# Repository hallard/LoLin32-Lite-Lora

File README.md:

# ESP32 LoLin32 Lite Lora Shield for RFM95 or RN2483

This shield is used to hold LoRa modules such as HopeRF [RFM95][4] or Mictrochip [RN2483][7] with WeMos ESP32 [LoLin32-Lite][22] boards it has the followong features:
- I2C Pullups placement
- Classic I2C connector with SCL/SDA and 3V3/GND reversable pin by solder pad
- Groove I2C connector
- Footprint for RFM95/96/98 or RN2483/RN2903 Lora module
- Footprint for choosing single Wire, SMA or u-FL Antenna type 
- 1 x WS2812B Type LED for visual indication
- 1 x Push Button
- Added footprint for Microchip 24AA02E64 64 bits serial number (DEVEUI)

Take care that WeMos has different Lolin32 boards, you need the [Lite][22] model. They Provide WeMos [Lolin32][20], [Lolin32 Pro][21] or this one [Lolin32 Lite][22]

You can also check the shield for the [Lolin32 (not Lite)][9] classic version. 

# Detailed Description

Look at the schematics for more informations.

SPI connexion is classic (MOSI/MISO/CLK), 

Other pins that may need be adapted into code (for example if you use TTN network gateway code) according to the following pinout

```
Lolin32-Lite   RFM9x Module
  IO5   <-------> SEL 
  IO19  <-------> MISO
  IO23  <-------> MOSI
  IO18  <-------> CLK
  IO27  <-------> DIO0
  IO26  <-------> DIO1
  IO4   <-------> DIO2
  IO25  <-------> RST
  IO35  <-------> DIO5

Lolin32-Lite   RN2xx3 Module
  IO4   <-------> RESET
  IO25  <-------> RX
  IO35  <-------> TX

Lolin32-Lite   Shield Feature
  IO12  <-------> I2C SCL
  IO14  <-------> I2C SDA
  IO13  <-------> WS2812 LEDS
  IO15  <-------> Push Button

Lolin32-Lite Free I/O
  IO0  -> Also used for Flash
  IO2 
  IO16 
  IO17
  IO22 -> On Board LoLin32-Lite LED
  IO32
  IO33 
  IO34 
```

**Do not forget to join (solder) the correct LoRa antenna trace** depending on module you place (RFM95 or RN2483), see picture below.

And as classic advice, **connect the LoRa antenna before powering** the board to avoid any damage to LoRa module

# Schematic  

# Firmware  

There is no firmware available, but you can have a large demo of features and a full working LoRa node (with RFM95) with this excellent [ESP32-Paxcounter](https://github.com/cyberman54/ESP32-Paxcounter/) software, it's a must see.

# Boards  

&nbsp;

You can order the PCB of this board at [PCBs.io][8]. PCBs.io give me some reward when you order my designed boards from their site. This is pretty good, because I can use these rewards to create and design new boards and order them for free, so if you don't care about PCB manufacturer please use PCBs.io.

# Assembled boards (TBD)

Not assembled yet but you can see approx what it looks like with the [Lolin32 (not Lite)][9] version. 

## With RFM95

## With RN2483

# License

This work is licensed under a [Creative Commons Attribution-NonCommercial 4.0 International License](http://creativecommons.org/licenses/by-nc/4.0/)    
If you want to do commercial stuff with this project, please contact [CH2i company](https://ch2i.eu/en#support) so we can organize an simple agreement.

# Misc

See news and other projects on my [blog][2] 
 
[2]: https://hallard.me
[3]: https://PCBs.io/share/zO3Ye
[4]: http://www.hoperf.com/rf_transceiver/lora/
[5]: https://github.com/hallard/ESP-1ch-Gateway/
[6]: https://github.com/matthijskooijman/arduino-lmic/pull/34
[7]: https://www.microchip.com/wwwproducts/en/RN2483
[8]: https://PCBs.io/share/4Qvx1
[9]: https://github.com/hallard/LoLin32-Lora

[10]: http://www.banggood.com/WeMos-LOLIN32-V1_0_0-WiFi-Bluetooth-Board-Based-ESP-32-4MB-FLASH-p-1164252.html

[20]: https://wiki.wemos.cc/products:lolin32:lolin32
[21]: https://wiki.wemos.cc/products:lolin32:lolin32_pro
[22]: https://wiki.wemos.cc/products:lolin32:lolin32_lite

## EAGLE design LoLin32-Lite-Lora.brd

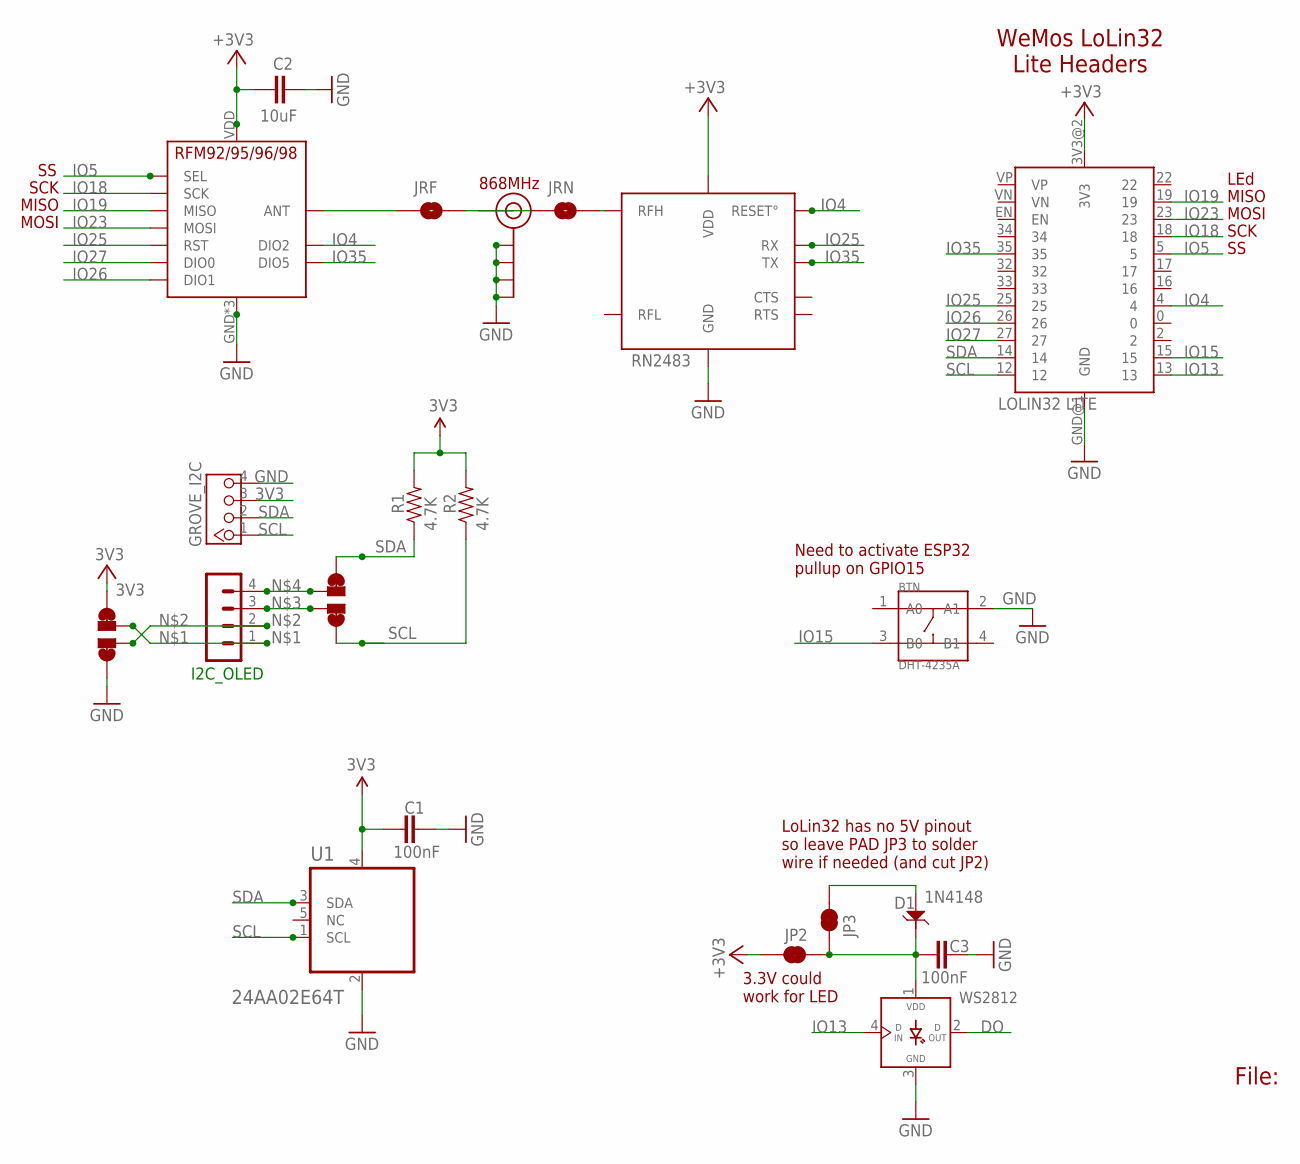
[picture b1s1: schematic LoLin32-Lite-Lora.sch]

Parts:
BTN: DHT-4235A; SW4-SMD-4.2X3.2X2.5MM
C1, C3: 100nF; 0805-CAP
C2: 10uF; 0805-CAP-LARGEPADS
D1: 1N4148; SOD123-2.7X1.6
GROVE_I2C: 4P-2.0; HW4-2.0
I2C_OLED: CON_HEADER_1X04'NO_LOCK'; 1X04_NO_LOCK
J$2: ANTENNATINY; SMA_UFL_PAD_TINY
JP2: RXLED; PAD-JUMPER-2-NC_BY_TRACE_YES_SILK
JP3: JUMPER-PAD-2-NC_BY_TRACE; PAD-JUMPER-2-NC_BY_TRACE_YES_SILK
JRF: JUMPER-PAD-2-NO; PAD-JUMPER-2-NO_NO_SILK
JRN: JUMPER-PAD-2-NO; PAD-JUMPER-2-NO_NO_SILK
R1, R2: 4.7K; 0805-RES
U1: 24AA02E64T; SOT95P270X145-5N
U$1: LOLIN32 LITE; LOLIN32_LITE
U$2, U$3: PAD-JUMPER-SWAPSWAP; PAD-JUMPER-SWAP
U$5: RFM95
U$7: RN2483; RN2483_NOGPIO_868
WS2812: WS2812B

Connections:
3V3: C1.1, C2.2, GROVE_I2C.3, JP2.2, R1.2, R2.2, U1.4 (VCC), U$1.3V3@2 (3V3), U$2.4, U$2.44 (4), U$5.VDD (VCC), U$7.VDD, U$7.VDD2 (VDD)
5V: D1.1, JP3.2
DO: WS2812.2 (DOUT)
GND: BTN.2 (A1), C1.2, C2.1, C3.2, GROVE_I2C.4, J$2.GND1 (GND), J$2.GND2 (GND), J$2.GND3 (GND), J$2.GND4 (GND), U1.2 (VSS), U$1.GND@1 (GND), U$2.1, U$2.11 (1), U$5.GND, U$5.GND1 (GND), U$5.GND2 (GND), U$7.GND, U$7.GND3 (GND), U$7.GND4 (GND), U$7.GND7 (GND), U$7.GND9 (GND), U$7.GND11 (GND), U$7.GND12 (GND), WS2812.3 (GND)
IO4: U$1.4, U$5.DIO2, U$7.RESET°
IO5: U$1.5, U$5.NSS (SEL)
IO13: U$1.13, WS2812.4 (DIN)
IO15: BTN.3 (B0), U$1.15
IO18: U$1.18, U$5.SCK
IO19: U$1.19, U$5.MISO
IO23: U$1.23, U$5.MOSI
IO25: U$1.25, U$5.RST, U$7.UART_RX (RX)
IO26: U$1.26, U$5.DIO1
IO27: U$1.27, U$5.DIO0
IO35: U$1.35, U$5.DIO5, U$7.UART_TX (TX)
unnamed: I2C_OLED.1, U$2.3
unnamed: I2C_OLED.2, U$2.2
unnamed: I2C_OLED.3, U$3.2
unnamed: I2C_OLED.4, U$3.3
unnamed: JRN.2, U$7.RFH
unnamed: JRF.1, U$5.ANT
unnamed: J$2.ANT1 (SIGNAL), J$2.ANT2 (SIGNAL), J$2.ANT3 (SIGNAL), JRF.2, JRN.1
SCL: GROVE_I2C.1, R2.1, U1.1 (SCL), U$1.12, U$3.1, U$3.11 (1)
SDA: GROVE_I2C.2, R1.1, U1.3 (SDA), U$1.14, U$3.4, U$3.44 (4)
VLED: C3.1, D1.2, JP2.1, JP3.1, WS2812.1 (VDD)

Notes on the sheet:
File:
WeMos LoLin32 Lite Headers
868MHz
MOSI
MISO
SCK
Need to activate ESP32 pullup on GPIO15
LEd
LoLin32 has no 5V pinout so leave PAD JP3 to solder wire if needed (and cut JP2)
3.3V could work for LED

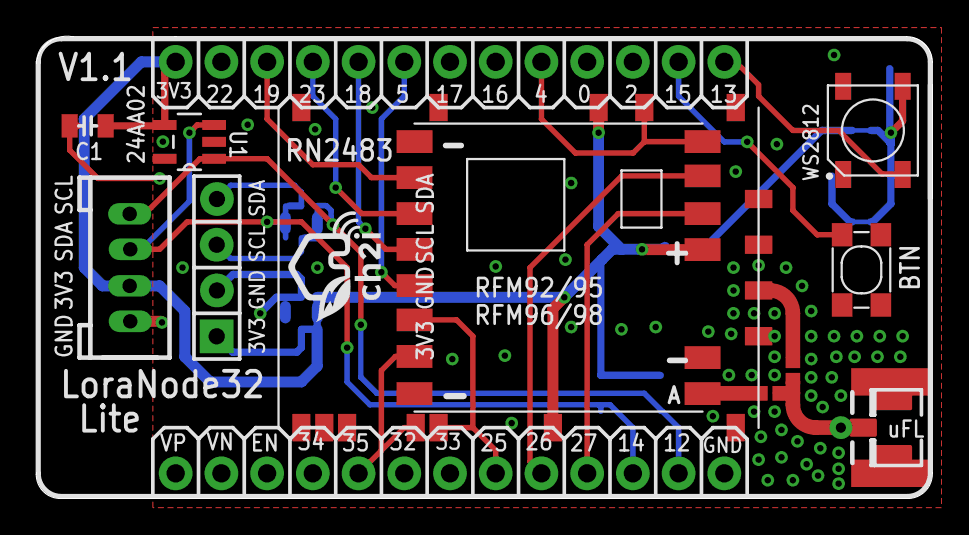
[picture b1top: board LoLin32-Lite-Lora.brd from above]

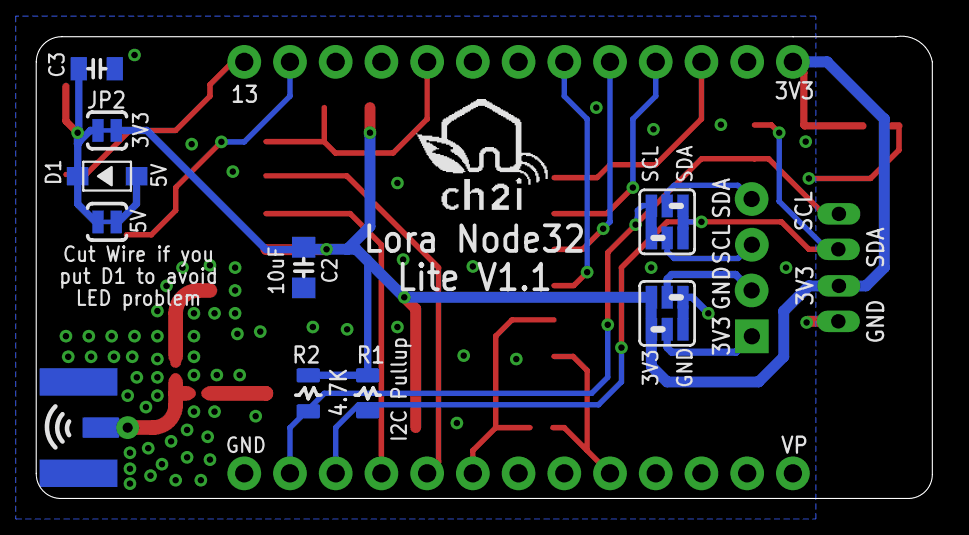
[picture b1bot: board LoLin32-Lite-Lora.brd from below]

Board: 2 copper layers, 49.8 x 25.7 mm, 23 parts (10 on the bottom side), 24 nets.

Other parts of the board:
U$4: LOGO_CH2I_75MM
U$6: LOGO_C2I_015

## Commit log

2018-03-27 :space_invader: Added .gitattributes
2018-03-27 Creation
2018-03-27 Added link to PAXcounter

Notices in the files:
parts and their libraries:
SparkFun-Passives: Licensing: Creative Commons ShareAlike 4.0 International - https://creativecommons.org/licenses/by-sa/4.0
